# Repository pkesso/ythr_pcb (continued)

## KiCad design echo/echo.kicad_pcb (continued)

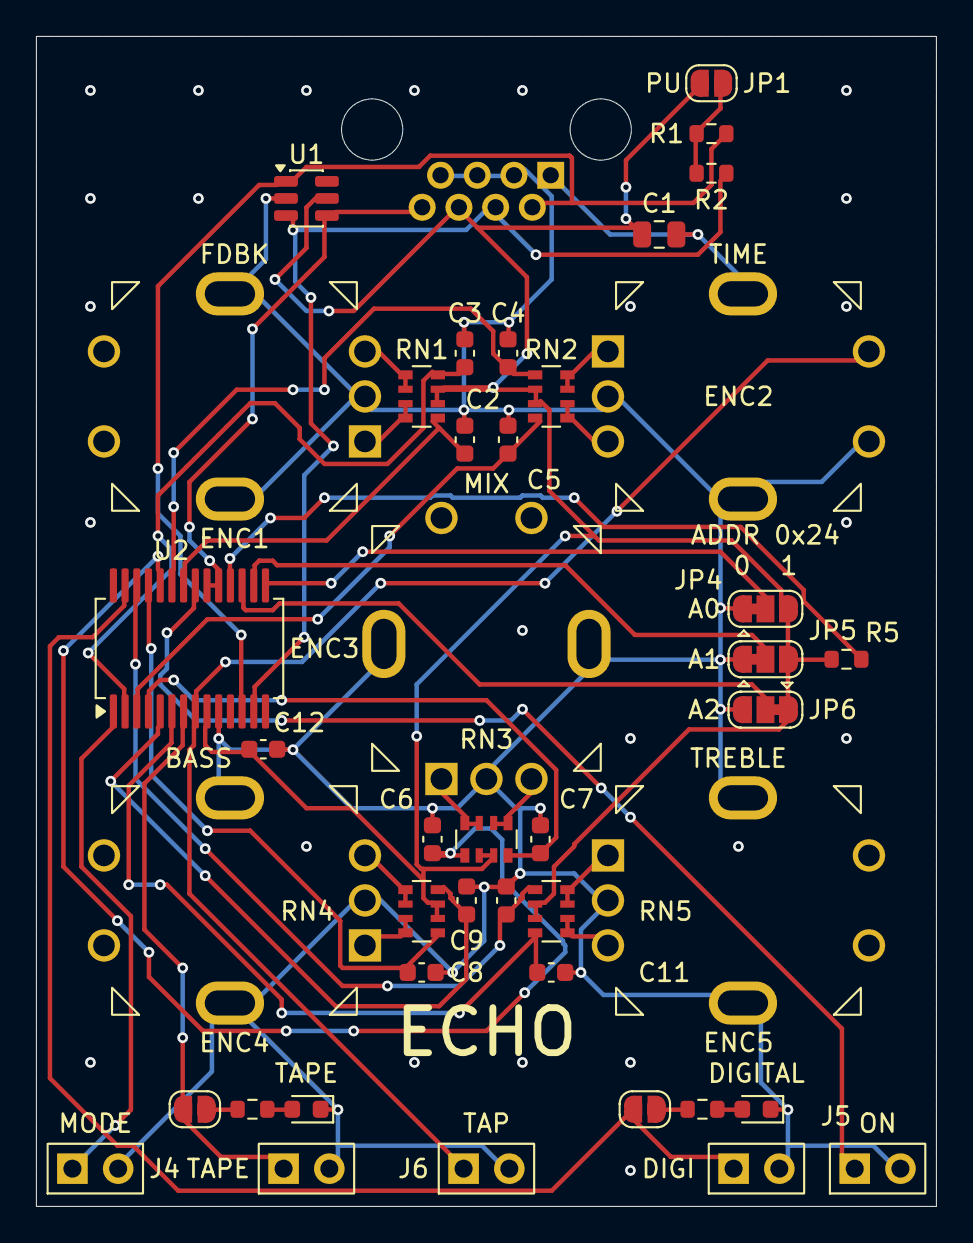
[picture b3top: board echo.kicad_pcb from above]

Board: 2 copper layers, 50.0 x 65.0 mm, 43 parts (1 on the bottom side), 39 nets.

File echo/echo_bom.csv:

Comment,Designator,Footprint,LCSC Part #
10u,C1,C_0805_2012Metric,C15850
10n,"C2,C3,C4,C5,C6,C7,C8,C9,C10,C11",C_0603_1608Metric,C57112
100n,C12,C_0603_1608Metric,C14663
red,"D1,D2",LED_0603_1608Metric,C2286
PEC11R-4015F-S0024,"ENC1,ENC2,ENC3,ENC4,ENC5",RotaryEncoder_Bourns_Vertical_PEC11R-4xxxF-Sxxxx,C143789
R-RJ45R08P-A004,J1,RJ45_Ckmtw_R-RJ45R08P-A004_Horizontal,C385834
10k,"R1,R2,R5",R_0603_1608Metric,C25804
470,"R3,R4",R_0603_1608Metric,C23179
4x10k,"RN1,RN2,RN3,RN4,RN5",R_Array_Convex_4x0603,C29718
SRV05-4,U1,SOT-23-6,C558418
MCP23017-E/SS,U2,SSOP-28_5.3x10.2mm_P0.65mm,C506653

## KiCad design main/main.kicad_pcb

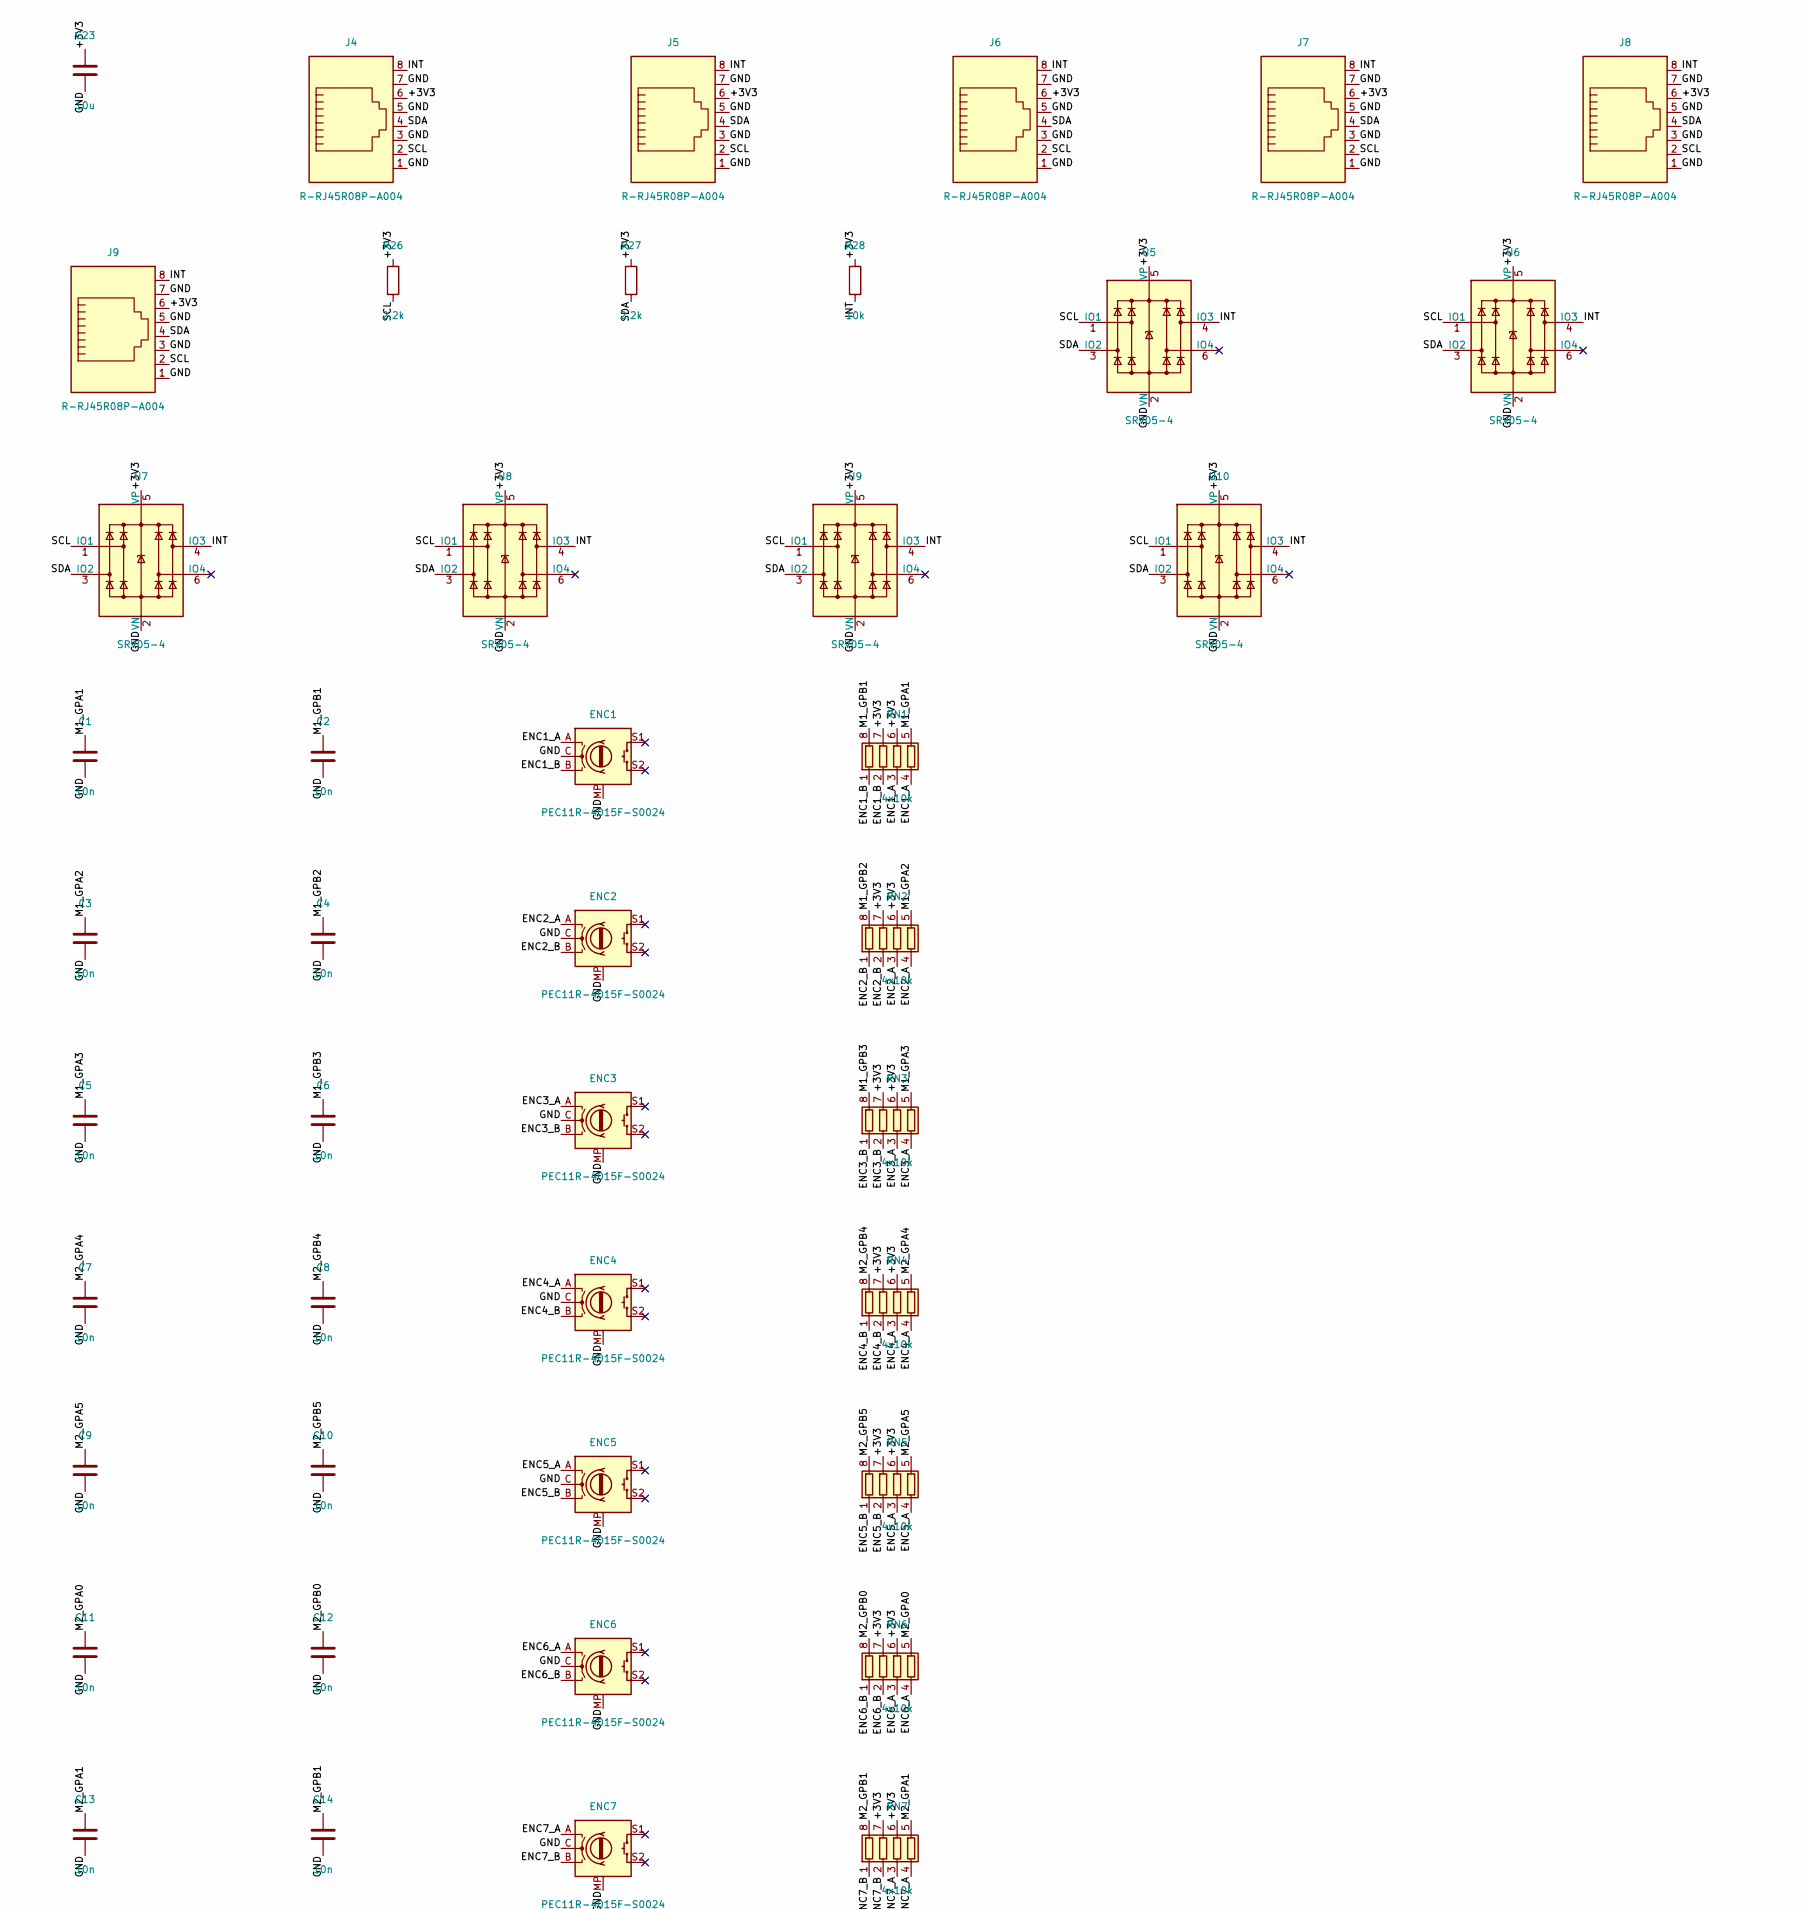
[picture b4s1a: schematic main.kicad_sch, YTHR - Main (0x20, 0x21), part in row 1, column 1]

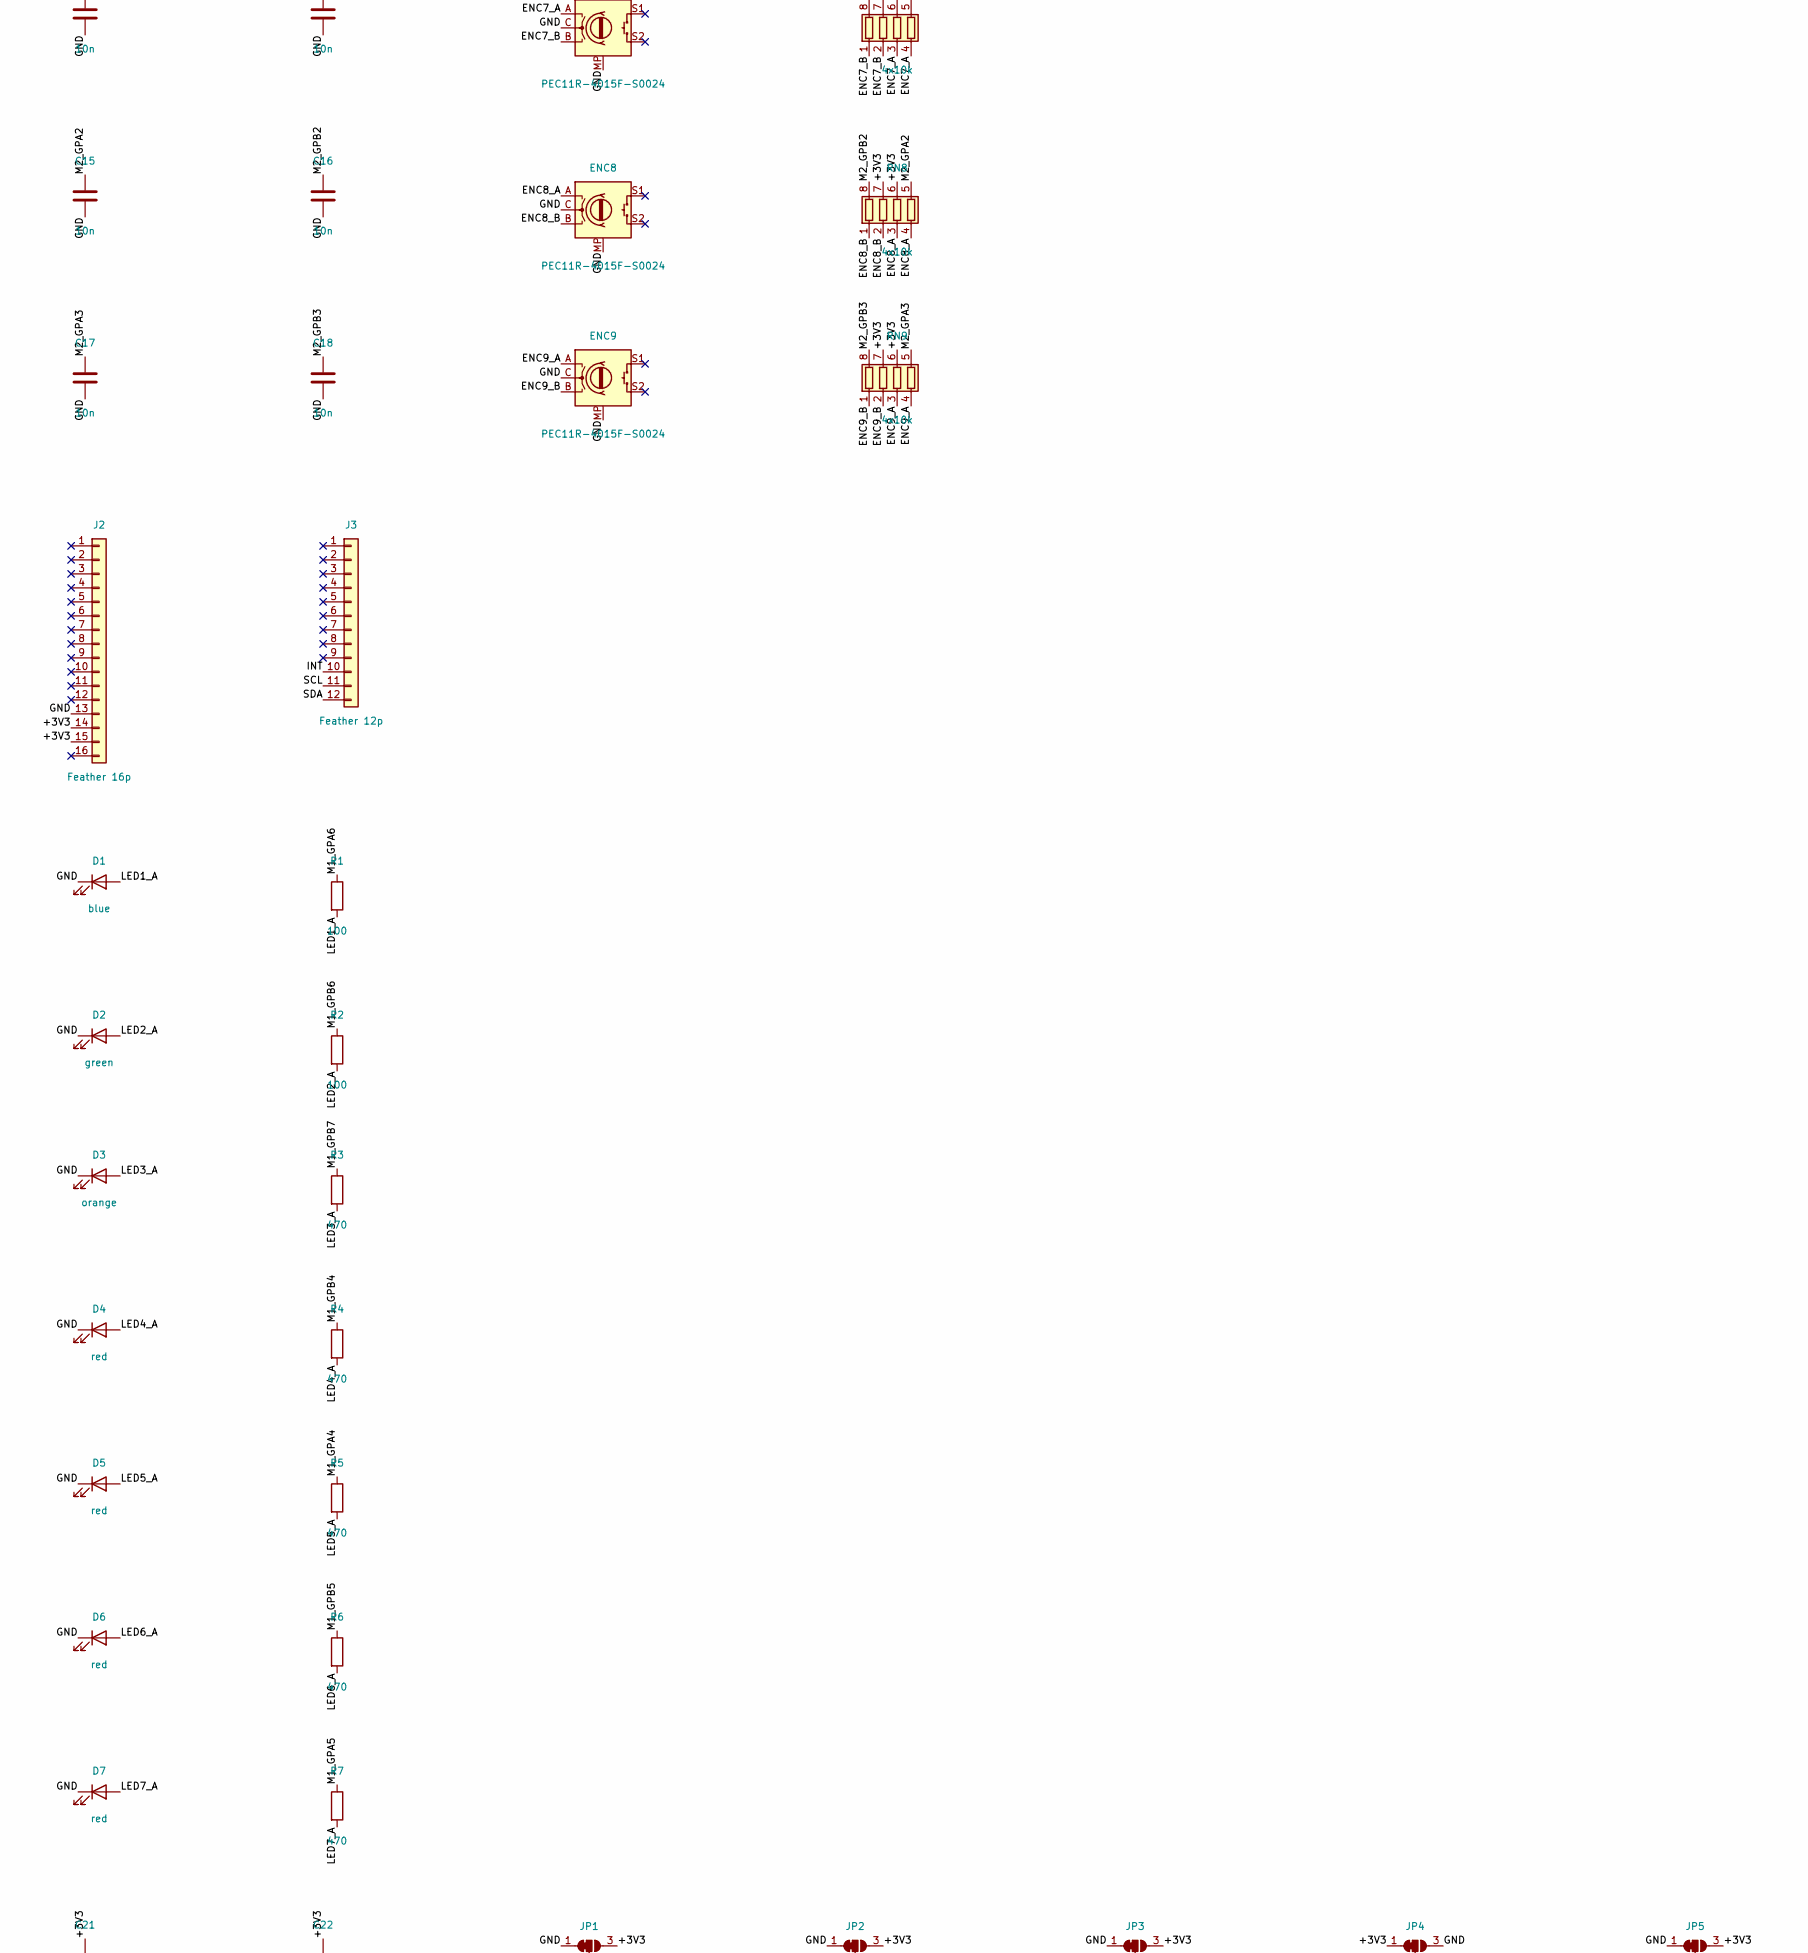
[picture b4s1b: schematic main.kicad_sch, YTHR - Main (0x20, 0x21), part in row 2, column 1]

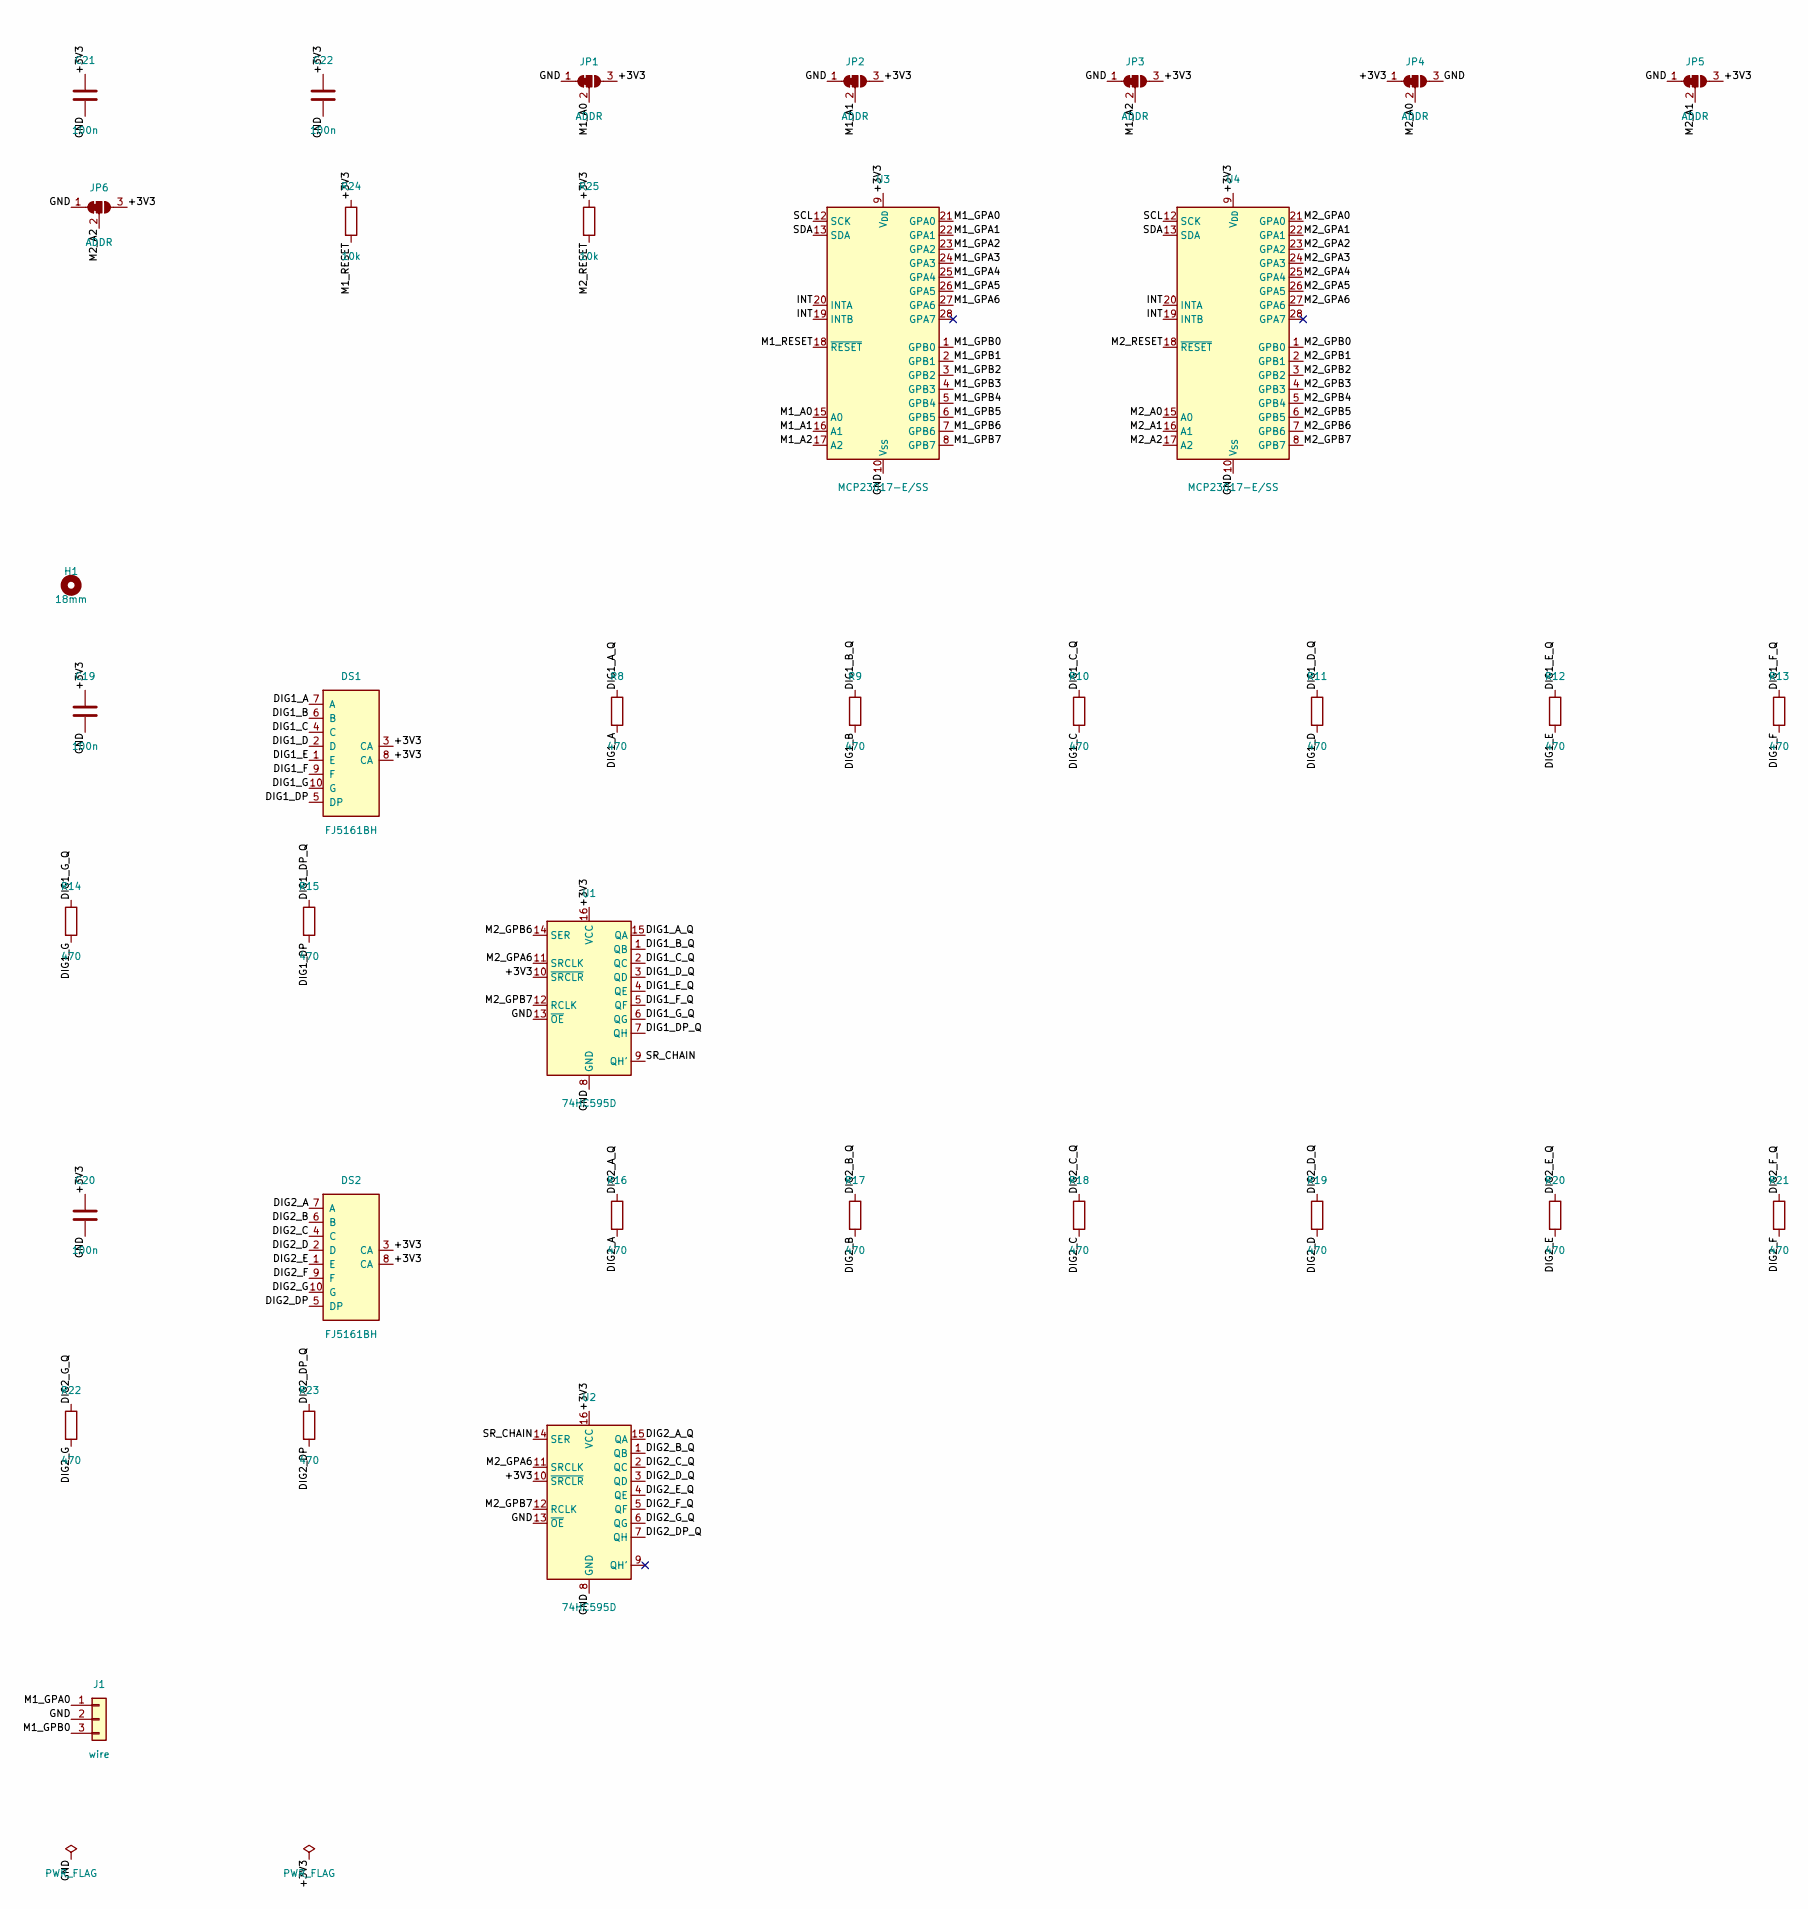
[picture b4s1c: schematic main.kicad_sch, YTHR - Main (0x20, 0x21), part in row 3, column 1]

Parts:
C1, C2, C3, C4, C5, C6, C7, C8, C9, C10, C11, C12, C13, C14, C15, C16, C17, C18: 10n; C_0603_1608Metric; LCSC C57112
C19, C20, C21, C22: 100n; C_0603_1608Metric; LCSC C14663
C23: 10u; C_0805_2012Metric; LCSC C15850
D1: blue; LED_0603_1608Metric; LCSC C965807
D2: green; LED_0805_2012Metric; LCSC C2297
D3: orange; LED_0603_1608Metric; LCSC C965800
D4, D5, D6, D7: red; LED_0603_1608Metric; LCSC C2286
DS1, DS2: FJ5161BH; 7SegmentLED_LTS6760_LTS6780; LCSC C8092
ENC1, ENC2, ENC3, ENC4, ENC5, ENC6, ENC7, ENC8, ENC9: PEC11R-4015F-S0024; RotaryEncoder_Bourns_Vertical_PEC11R-4xxxF-Sxxxx; LCSC C143789
H1: 18mm; Hole_18mm_NoHead
J1: wire; WirePads_1x03_P2.54mm_Drill1.0mm
J2: Feather 16p; PinSocket_1x16_P2.54mm_Vertical
J3: Feather 12p; PinSocket_1x12_P2.54mm_Vertical
J4, J5, J6, J7, J8, J9: R-RJ45R08P-A004; RJ45_Ckmtw_R-RJ45R08P-A004_Horizontal
JP1, JP2, JP3, JP4, JP5, JP6: ADDR; SolderJumper-3_P1.3mm_Bridged12_RoundedPad1.0x1.5mm
R1, R2: 100; R_0603_1608Metric; LCSC C22775
R3, R4, R5, R6, R7, R8, R9, R10, R11, R12, R13, R14, R15, R16, R17, R18, R19, R20, R21, R22, R23: 470; R_0603_1608Metric; LCSC C23179
R24, R25, R28: 10k; R_0603_1608Metric; LCSC C25804
R26, R27: 2.2k; R_0603_1608Metric; LCSC C4190
RN1, RN2, RN3, RN4, RN5, RN6, RN7, RN8, RN9: 4x10k; R_Array_Convex_4x0603; LCSC C29718
U1, U2: 74HC595D; SOIC-16_3.9x9.9mm_P1.27mm; LCSC C5947
U3, U4: MCP23017-E/SS; SSOP-28_5.3x10.2mm_P0.65mm; LCSC C506653
U5, U6, U7, U8, U9, U10: SRV05-4; SOT-23-6; LCSC C558418

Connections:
/+3V3: C19.1, C20.1, C21.1, C22.1, C23.1, DS1.3 (CA), DS1.8 (CA), DS2.3 (CA), DS2.8 (CA), J2.14, J2.15, J4.6, J5.6, J6.6, J7.6, J8.6, J9.6, JP1.3 (B), JP2.3 (B), JP3.3 (B), JP4.1 (A), JP5.3 (B), JP6.3 (B), R24.1, R25.1, R26.1, R27.1, R28.1, RN1.6 (R3.2), RN1.7 (R2.2), RN2.6 (R3.2), RN2.7 (R2.2), RN3.6 (R3.2), RN3.7 (R2.2), RN4.6 (R3.2), RN4.7 (R2.2), RN5.6 (R3.2), RN5.7 (R2.2), RN6.6 (R3.2), RN6.7 (R2.2), RN7.6 (R3.2), RN7.7 (R2.2), RN8.6 (R3.2), RN8.7 (R2.2), RN9.6 (R3.2), RN9.7 (R2.2), U1.10 (~SRCLR), U1.16 (VCC), U2.10 (~SRCLR), U2.16 (VCC), U3.9 (V_{DD}), U4.9 (V_{DD}), U5.5 (VP), U6.5 (VP), U7.5 (VP), U8.5 (VP), U9.5 (VP), U10.5 (VP)
/DIG1_A: DS1.7 (A), R8.2
/DIG1_A_Q: R8.1, U1.15 (QA)
/DIG1_B: DS1.6 (B), R9.2
/DIG1_B_Q: R9.1, U1.1 (QB)
/DIG1_C: DS1.4 (C), R10.2
/DIG1_C_Q: R10.1, U1.2 (QC)
/DIG1_D: DS1.2 (D), R11.2
/DIG1_DP: DS1.5 (DP), R15.2
/DIG1_DP_Q: R15.1, U1.7 (QH)
/DIG1_D_Q: R11.1, U1.3 (QD)
/DIG1_E: DS1.1 (E), R12.2
/DIG1_E_Q: R12.1, U1.4 (QE)
/DIG1_F: DS1.9 (F), R13.2
/DIG1_F_Q: R13.1, U1.5 (QF)
/DIG1_G: DS1.10 (G), R14.2
/DIG1_G_Q: R14.1, U1.6 (QG)
/DIG2_A: DS2.7 (A), R16.2
/DIG2_A_Q: R16.1, U2.15 (QA)
/DIG2_B: DS2.6 (B), R17.2
/DIG2_B_Q: R17.1, U2.1 (QB)
/DIG2_C: DS2.4 (C), R18.2
/DIG2_C_Q: R18.1, U2.2 (QC)
/DIG2_D: DS2.2 (D), R19.2
/DIG2_DP: DS2.5 (DP), R23.2
/DIG2_DP_Q: R23.1, U2.7 (QH)
/DIG2_D_Q: R19.1, U2.3 (QD)
/DIG2_E: DS2.1 (E), R20.2
/DIG2_E_Q: R20.1, U2.4 (QE)
/DIG2_F: DS2.9 (F), R21.2
/DIG2_F_Q: R21.1, U2.5 (QF)
/DIG2_G: DS2.10 (G), R22.2
/DIG2_G_Q: R22.1, U2.6 (QG)
/ENC1_A: ENC1.A, RN1.3 (R3.1), RN1.4 (R4.1)
/ENC1_B: ENC1.B, RN1.1 (R1.1), RN1.2 (R2.1)
/ENC2_A: ENC2.A, RN2.3 (R3.1), RN2.4 (R4.1)
/ENC2_B: ENC2.B, RN2.1 (R1.1), RN2.2 (R2.1)
/ENC3_A: ENC3.A, RN3.3 (R3.1), RN3.4 (R4.1)
/ENC3_B: ENC3.B, RN3.1 (R1.1), RN3.2 (R2.1)
/ENC4_A: ENC4.A, RN4.3 (R3.1), RN4.4 (R4.1)
/ENC4_B: ENC4.B, RN4.1 (R1.1), RN4.2 (R2.1)
/ENC5_A: ENC5.A, RN5.3 (R3.1), RN5.4 (R4.1)
/ENC5_B: ENC5.B, RN5.1 (R1.1), RN5.2 (R2.1)
/ENC6_A: ENC6.A, RN6.3 (R3.1), RN6.4 (R4.1)
/ENC6_B: ENC6.B, RN6.1 (R1.1), RN6.2 (R2.1)
/ENC7_A: ENC7.A, RN7.3 (R3.1), RN7.4 (R4.1)
/ENC7_B: ENC7.B, RN7.1 (R1.1), RN7.2 (R2.1)
/ENC8_A: ENC8.A, RN8.3 (R3.1), RN8.4 (R4.1)
/ENC8_B: ENC8.B, RN8.1 (R1.1), RN8.2 (R2.1)
/ENC9_A: ENC9.A, RN9.3 (R3.1), RN9.4 (R4.1)
/ENC9_B: ENC9.B, RN9.1 (R1.1), RN9.2 (R2.1)
/GND: C1.2, C2.2, C3.2, C4.2, C5.2, C6.2, C7.2, C8.2, C9.2, C10.2, C11.2, C12.2, C13.2, C14.2, C15.2, C16.2, C17.2, C18.2, C19.2, C20.2, C21.2, C22.2, C23.2, D1.1 (K), D2.1 (K), D3.1 (K), D4.1 (K), D5.1 (K), D6.1 (K), D7.1 (K), ENC1.C, ENC1.MP, ENC2.C, ENC2.MP, ENC3.C, ENC3.MP, ENC4.C, ENC4.MP, ENC5.C, ENC5.MP, ENC6.C, ENC6.MP, ENC7.C, ENC7.MP, ENC8.C, ENC8.MP, ENC9.C, ENC9.MP, J1.2, J2.13, J4.1, J4.3, J4.5, J4.7, J5.1, J5.3, J5.5, J5.7, J6.1, J6.3, J6.5, J6.7, J7.1, J7.3, J7.5, J7.7, J8.1, J8.3, J8.5, J8.7, J9.1, J9.3, J9.5, J9.7, JP1.1 (A), JP2.1 (A), JP3.1 (A), JP4.3 (B), JP5.1 (A), JP6.1 (A), U1.8 (GND), U1.13 (~OE), U2.8 (GND), U2.13 (~OE), U3.10 (V_{SS}), U4.10 (V_{SS}), U5.2 (VN), U6.2 (VN), U7.2 (VN), U8.2 (VN), U9.2 (VN), U10.2 (VN)
/INT: J3.10, J4.8, J5.8, J6.8, J7.8, J8.8, J9.8, R28.2, U3.19 (INTB), U3.20 (INTA), U4.19 (INTB), U4.20 (INTA), U5.4 (IO3), U6.4 (IO3), U7.4 (IO3), U8.4 (IO3), U9.4 (IO3), U10.4 (IO3)
/LED1_A: D1.2 (A), R1.2
/LED2_A: D2.2 (A), R2.2
/LED3_A: D3.2 (A), R3.2
/LED4_A: D4.2 (A), R4.2
/LED5_A: D5.2 (A), R5.2
/LED6_A: D6.2 (A), R6.2
/LED7_A: D7.2 (A), R7.2
/M1_A0: JP1.2 (C), U3.15 (A0)
/M1_A1: JP2.2 (C), U3.16 (A1)
/M1_A2: JP3.2 (C), U3.17 (A2)
/M1_GPA0: J1.1, U3.21 (GPA0)
/M1_GPA1: C1.1, RN1.5 (R4.2), U3.22 (GPA1)
/M1_GPA2: C3.1, RN2.5 (R4.2), U3.23 (GPA2)
/M1_GPA3: C5.1, RN3.5 (R4.2), U3.24 (GPA3)
/M1_GPA4: R5.1, U3.25 (GPA4)
/M1_GPA5: R7.1, U3.26 (GPA5)
/M1_GPA6: R1.1, U3.27 (GPA6)
/M1_GPB0: J1.3, U3.1 (GPB0)
/M1_GPB1: C2.1, RN1.8 (R1.2), U3.2 (GPB1)
/M1_GPB2: C4.1, RN2.8 (R1.2), U3.3 (GPB2)
/M1_GPB3: C6.1, RN3.8 (R1.2), U3.4 (GPB3)
/M1_GPB4: R4.1, U3.5 (GPB4)
/M1_GPB5: R6.1, U3.6 (GPB5)
/M1_GPB6: R2.1, U3.7 (GPB6)
/M1_GPB7: R3.1, U3.8 (GPB7)
/M1_RESET: R24.2, U3.18 (~RESET)
/M2_A0: JP4.2 (C), U4.15 (A0)
/M2_A1: JP5.2 (C), U4.16 (A1)
/M2_A2: JP6.2 (C), U4.17 (A2)
/M2_GPA0: C11.1, RN6.5 (R4.2), U4.21 (GPA0)
/M2_GPA1: C13.1, RN7.5 (R4.2), U4.22 (GPA1)
/M2_GPA2: C15.1, RN8.5 (R4.2), U4.23 (GPA2)
/M2_GPA3: C17.1, RN9.5 (R4.2), U4.24 (GPA3)
/M2_GPA4: C7.1, RN4.5 (R4.2), U4.25 (GPA4)
/M2_GPA5: C9.1, RN5.5 (R4.2), U4.26 (GPA5)
/M2_GPA6: U1.11 (SRCLK), U2.11 (SRCLK), U4.27 (GPA6)
/M2_GPB0: C12.1, RN6.8 (R1.2), U4.1 (GPB0)
/M2_GPB1: C14.1, RN7.8 (R1.2), U4.2 (GPB1)
/M2_GPB2: C16.1, RN8.8 (R1.2), U4.3 (GPB2)
/M2_GPB3: C18.1, RN9.8 (R1.2), U4.4 (GPB3)
/M2_GPB4: C8.1, RN4.8 (R1.2), U4.5 (GPB4)
/M2_GPB5: C10.1, RN5.8 (R1.2), U4.6 (GPB5)
/M2_GPB6: U1.14 (SER), U4.7 (GPB6)
/M2_GPB7: U1.12 (RCLK), U2.12 (RCLK), U4.8 (GPB7)
/M2_RESET: R25.2, U4.18 (~RESET)
/SCL: J3.11, J4.2, J5.2, J6.2, J7.2, J8.2, J9.2, R26.2, U3.12 (SCK), U4.12 (SCK), U5.1 (IO1), U6.1 (IO1), U7.1 (IO1), U8.1 (IO1), U9.1 (IO1), U10.1 (IO1)
/SDA: J3.12, J4.4, J5.4, J6.4, J7.4, J8.4, J9.4, R27.2, U3.13 (SDA), U4.13 (SDA), U5.3 (IO2), U6.3 (IO2), U7.3 (IO2), U8.3 (IO2), U9.3 (IO2), U10.3 (IO2)
/SR_CHAIN: U1.9 (QH'), U2.14 (SER)

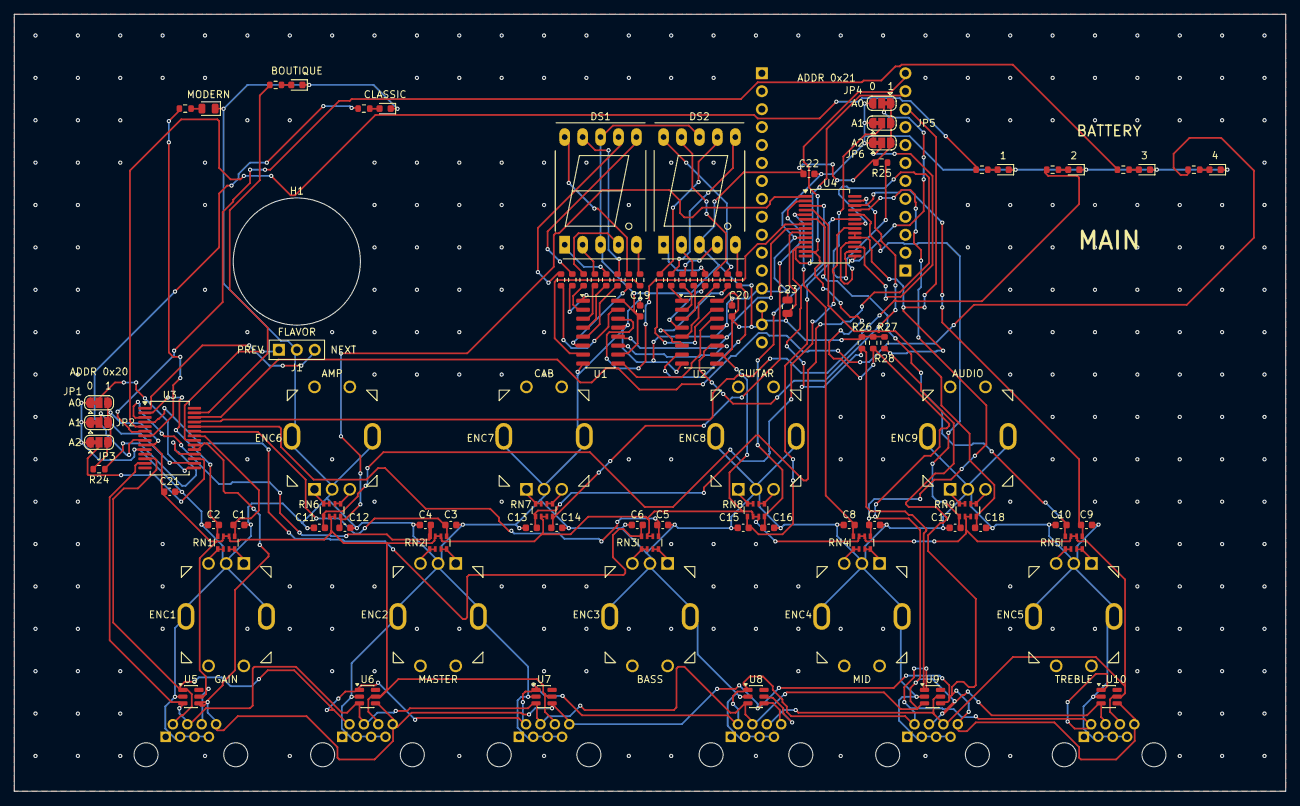
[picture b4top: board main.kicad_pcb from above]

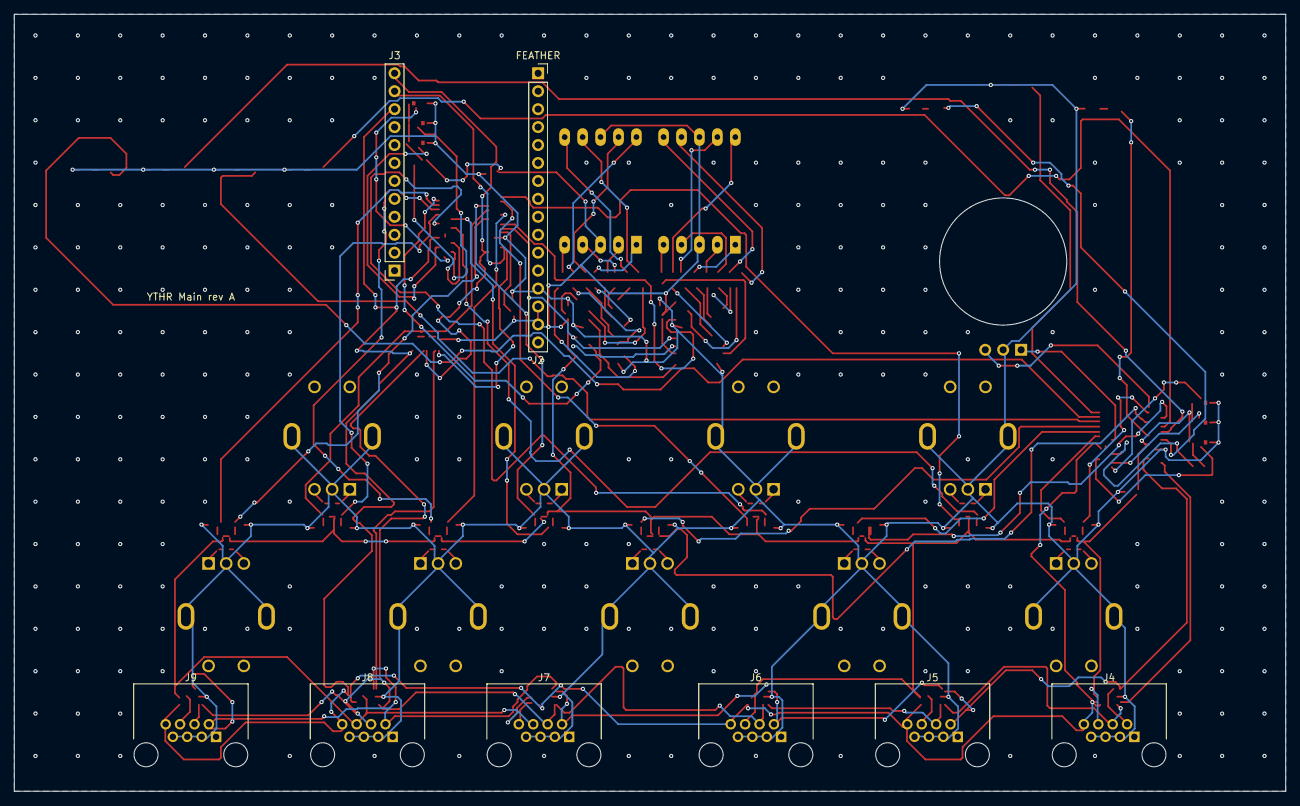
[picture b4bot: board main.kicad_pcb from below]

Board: 2 copper layers, 180.0 x 110.0 mm, 104 parts (8 on the bottom side), 101 nets.

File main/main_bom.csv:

Comment,Designator,Footprint,LCSC Part #
10n,"C1,C2,C3,C4,C5,C6,C7,C8,C9,C10,C11,C12,C13,C14,C15,C16,C17,C18",C_0603_1608Metric,C57112
100n,"C19,C20,C21,C22",C_0603_1608Metric,C14663
10u,C23,C_0805_2012Metric,C15850
blue,D1,LED_0603_1608Metric,C965807
green,D2,LED_0805_2012Metric,C2297
orange,D3,LED_0603_1608Metric,C965800
red,"D4,D5,D6,D7",LED_0603_1608Metric,C2286
FJ5161BH,"DS1,DS2",7SegmentLED_LTS6760_LTS6780,C8092
PEC11R-4015F-S0024,"ENC1,ENC2,ENC3,ENC4,ENC5,ENC6,ENC7,ENC8,ENC9",RotaryEncoder_Bourns_Vertical_PEC11R-4xxxF-Sxxxx,C143789
100,"R1,R2",R_0603_1608Metric,C22775
470,"R3,R4,R5,R6,R7,R8,R9,R10,R11,R12,R13,R14,R15,R16,R17,R18,R19,R20,R21,R22,R23",R_0603_1608Metric,C23179
10k,"R24,R25,R28",R_0603_1608Metric,C25804
2.2k,"R26,R27",R_0603_1608Metric,C4190
4x10k,"RN1,RN2,RN3,RN4,RN5,RN6,RN7,RN8,RN9",R_Array_Convex_4x0603,C29718
74HC595D,"U1,U2",SOIC-16_3.9x9.9mm_P1.27mm,C5947
MCP23017-E/SS,"U3,U4",SSOP-28_5.3x10.2mm_P0.65mm,C506653
SRV05-4,"U5,U6,U7,U8,U9,U10",SOT-23-6,C558418
